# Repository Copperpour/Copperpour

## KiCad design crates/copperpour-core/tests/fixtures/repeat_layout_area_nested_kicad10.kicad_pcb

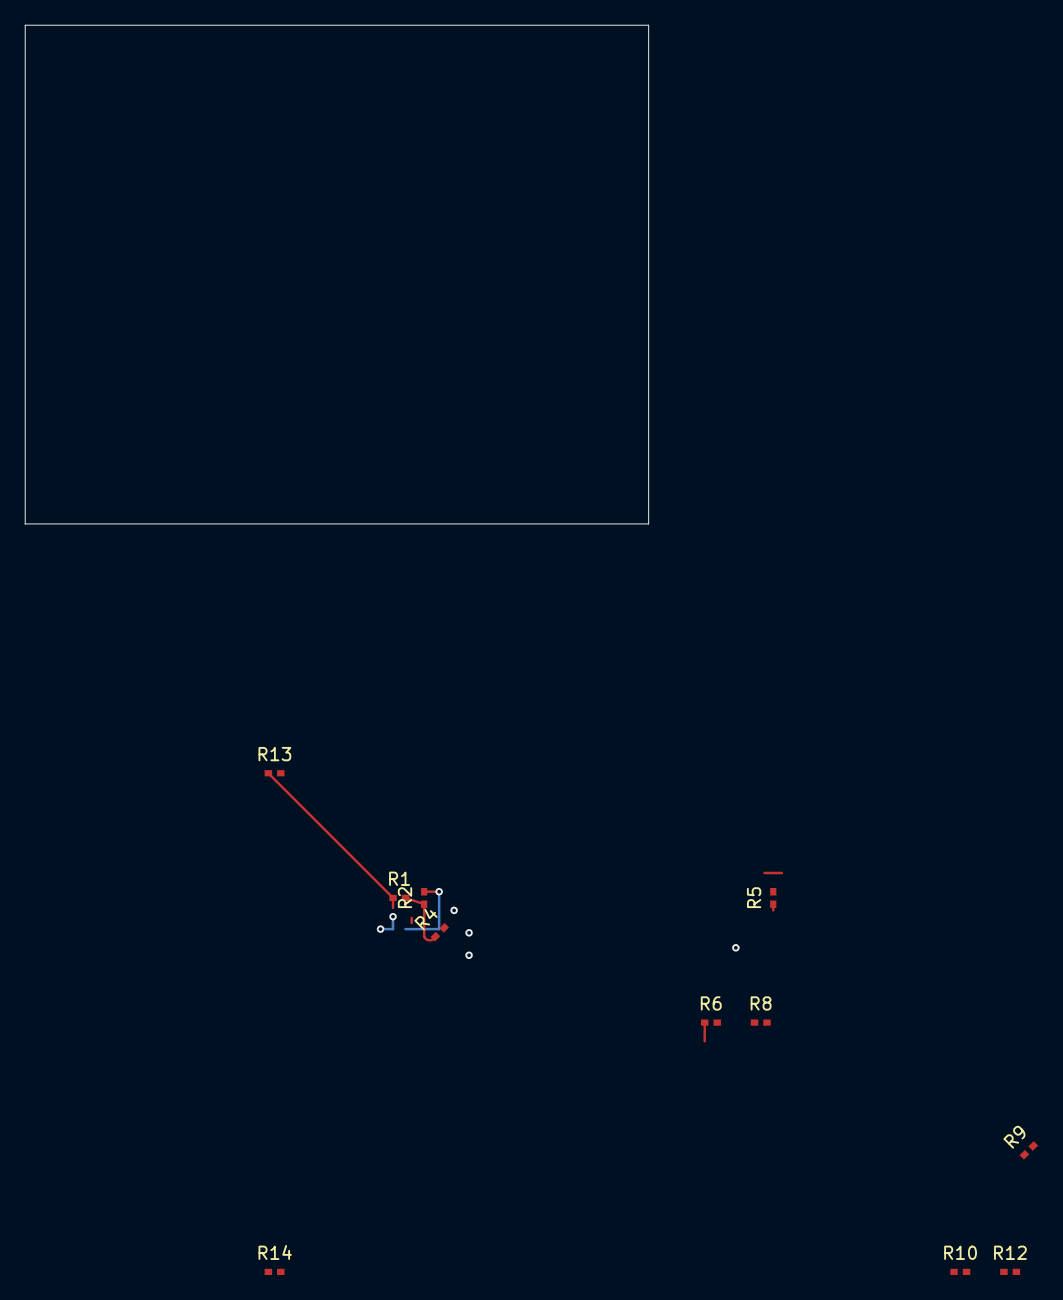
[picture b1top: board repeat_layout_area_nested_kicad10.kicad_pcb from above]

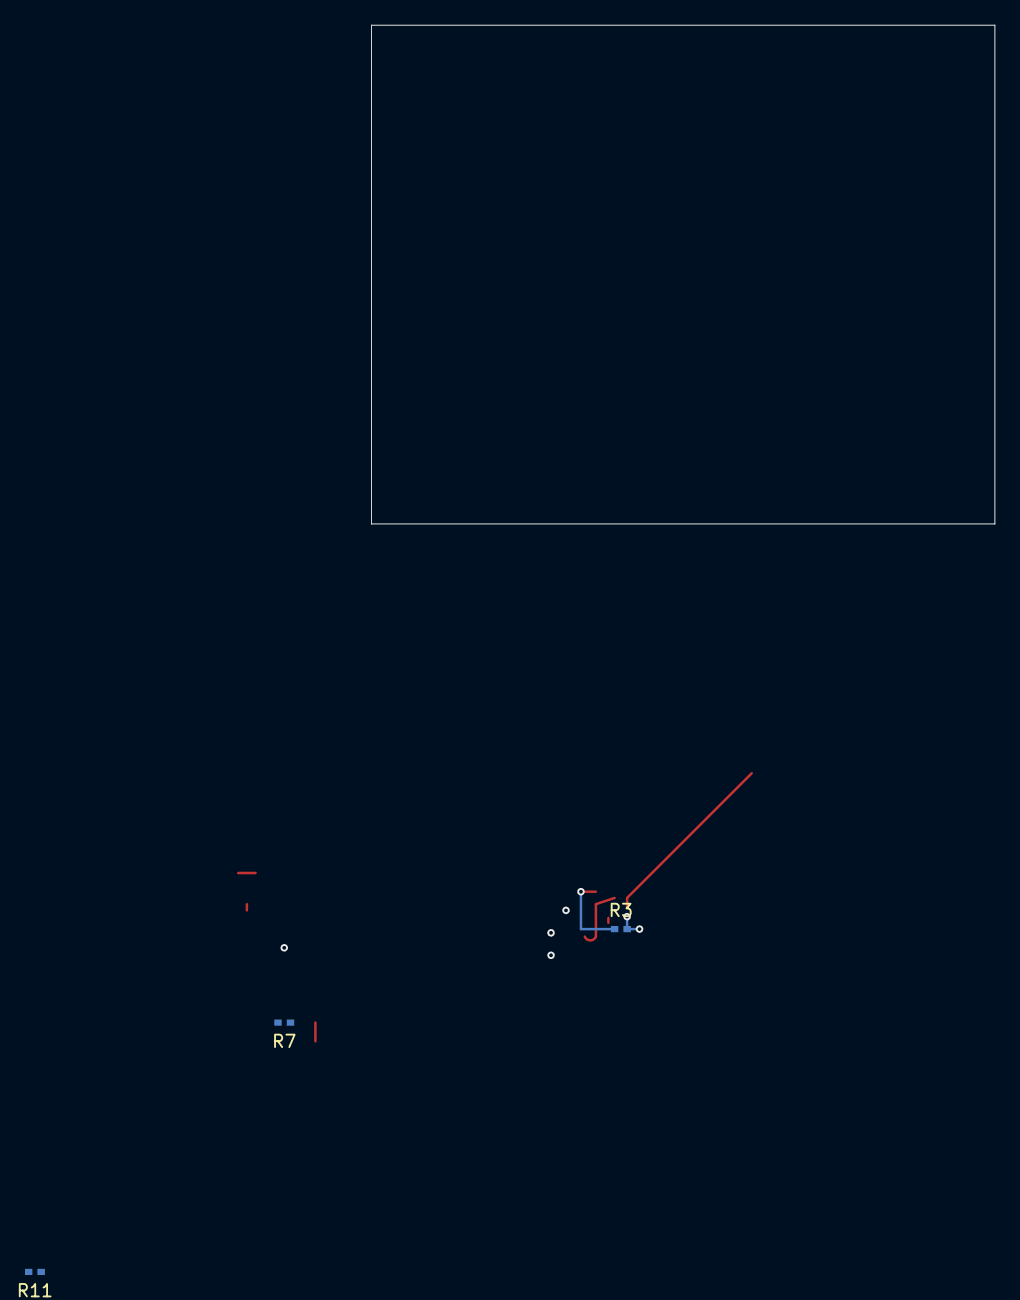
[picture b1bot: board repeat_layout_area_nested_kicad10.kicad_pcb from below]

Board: 2 copper layers, 50.0 x 40.0 mm, 14 parts (3 on the bottom side), 8 nets.

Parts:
R1, R2, R3, R4, R5, R6, R7, R8, R9, R10, R11, R12, R13, R14: 10k; R_0402

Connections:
/Channel 1/IN: R1.1, R13.1
/Channel 1/MID: R1.2, R2.1, R4.1
/Channel 1/OUT: R2.2, R3.1
/Channel 2/MID: R5.2, R6.1, R8.1
/Channel 2/OUT: R6.2, R7.1
/Channel 3/MID: R9.2, R10.1, R12.1
/Channel 3/OUT: R10.2, R11.1
GND: R3.2, R4.2, R7.2, R8.2, R11.2, R12.2, R13.2, R14.2

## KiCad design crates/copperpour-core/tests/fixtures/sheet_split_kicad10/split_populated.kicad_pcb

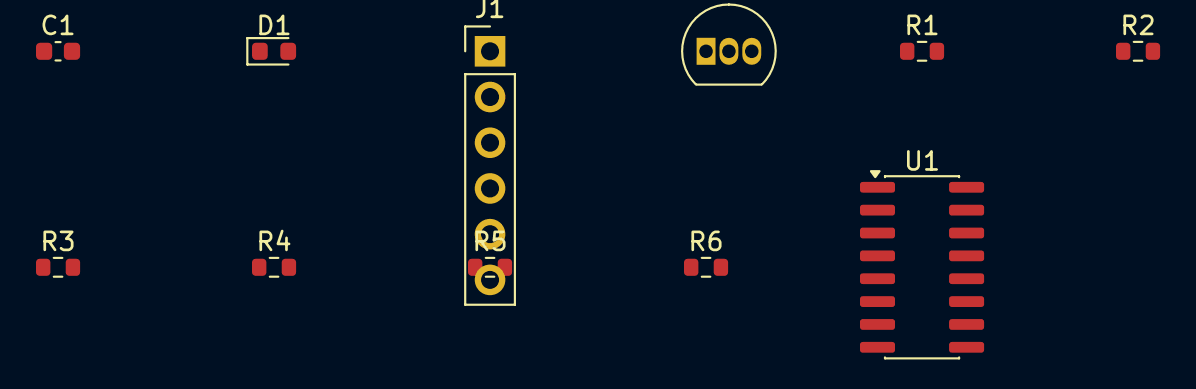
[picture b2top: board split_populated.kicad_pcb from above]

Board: 2 copper layers, 11 parts (0 on the bottom side), 10 nets, no tracks yet.

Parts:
C1: 100n; C_0603_1608Metric
D1: LED; LED_0603_1608Metric
J1: Conn_01x06; PinHeader_1x06_P2.54mm_Vertical
Q1: BC547; TO-92_Inline
R1: 1k; R_0603_1608Metric
R2: 330; R_0603_1608Metric
R3, R4, R5, R6: 10k; R_0603_1608Metric
U1: 74HC595; SOIC-16_3.9x9.9mm_P1.27mm

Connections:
+5V: C1.1, J1.1, R2.1, R3.1, R4.1, R5.1, R6.1, U1.16
/LED_EN: R1.1, U1.15
/LED_K: D1.1, Q1.1
GND: C1.2, J1.2, Q1.3, U1.8, U1.13
unnamed: D1.2, R2.2
unnamed: J1.3, R3.2, U1.14
unnamed: J1.4, R4.2, U1.11
unnamed: J1.5, R5.2, U1.10
unnamed: J1.6, R6.2, U1.12
unnamed: Q1.2, R1.2
